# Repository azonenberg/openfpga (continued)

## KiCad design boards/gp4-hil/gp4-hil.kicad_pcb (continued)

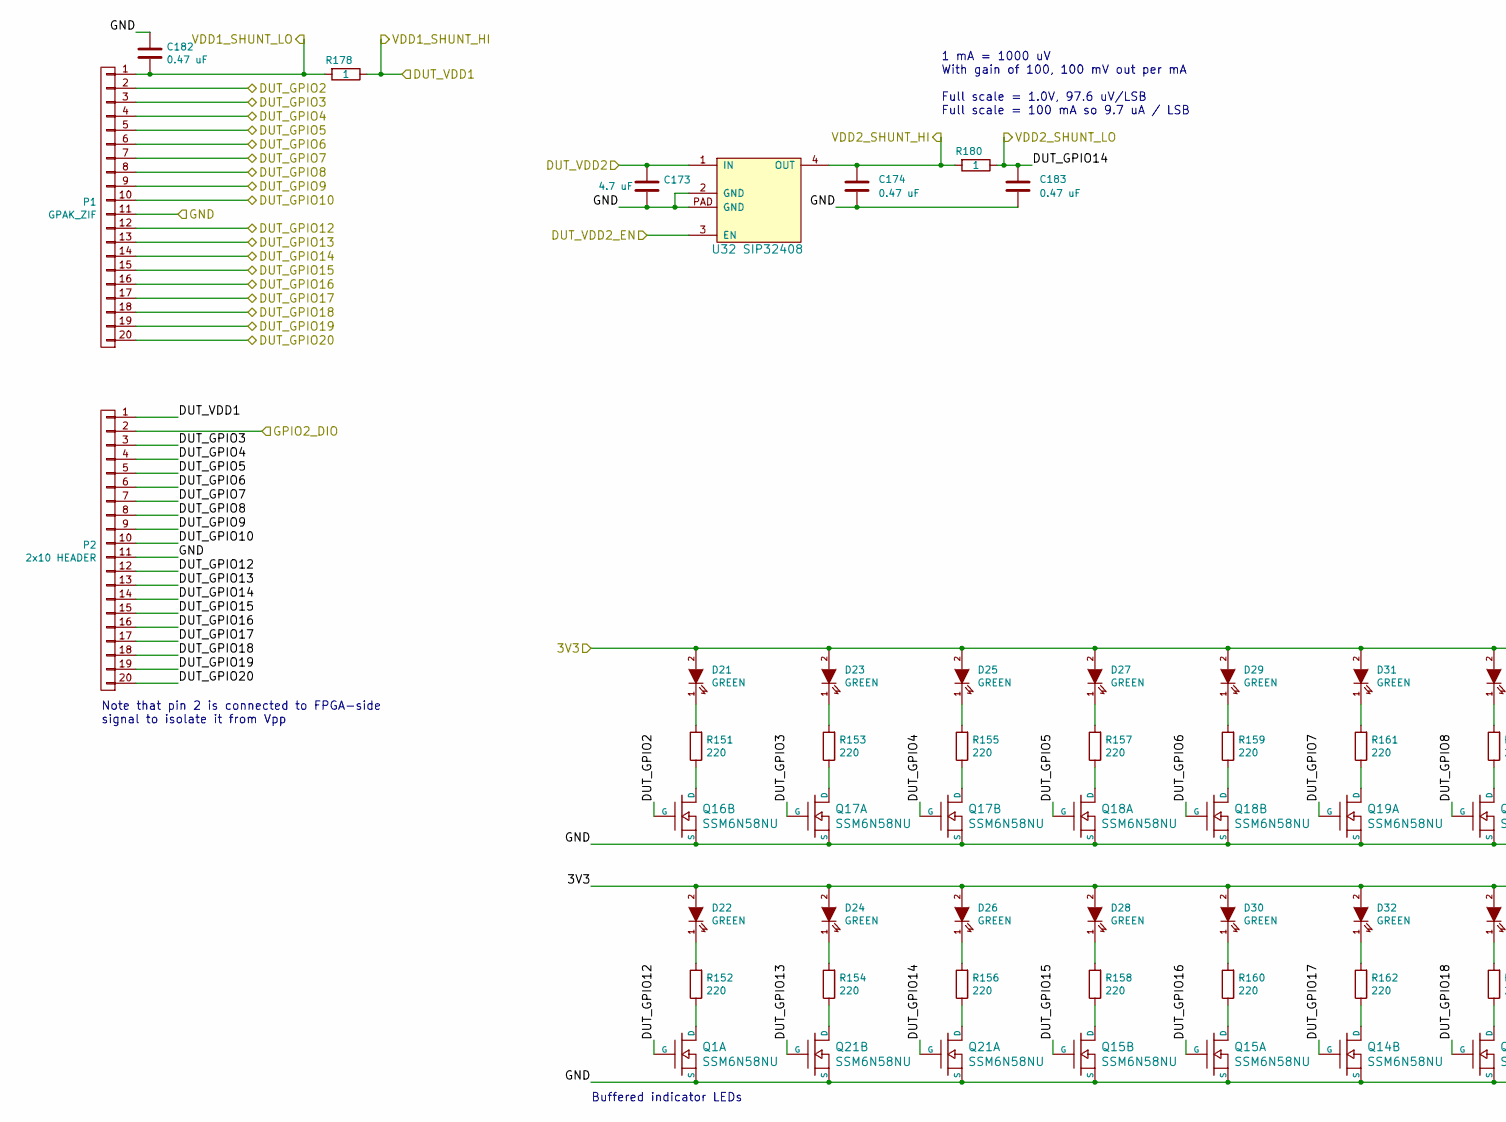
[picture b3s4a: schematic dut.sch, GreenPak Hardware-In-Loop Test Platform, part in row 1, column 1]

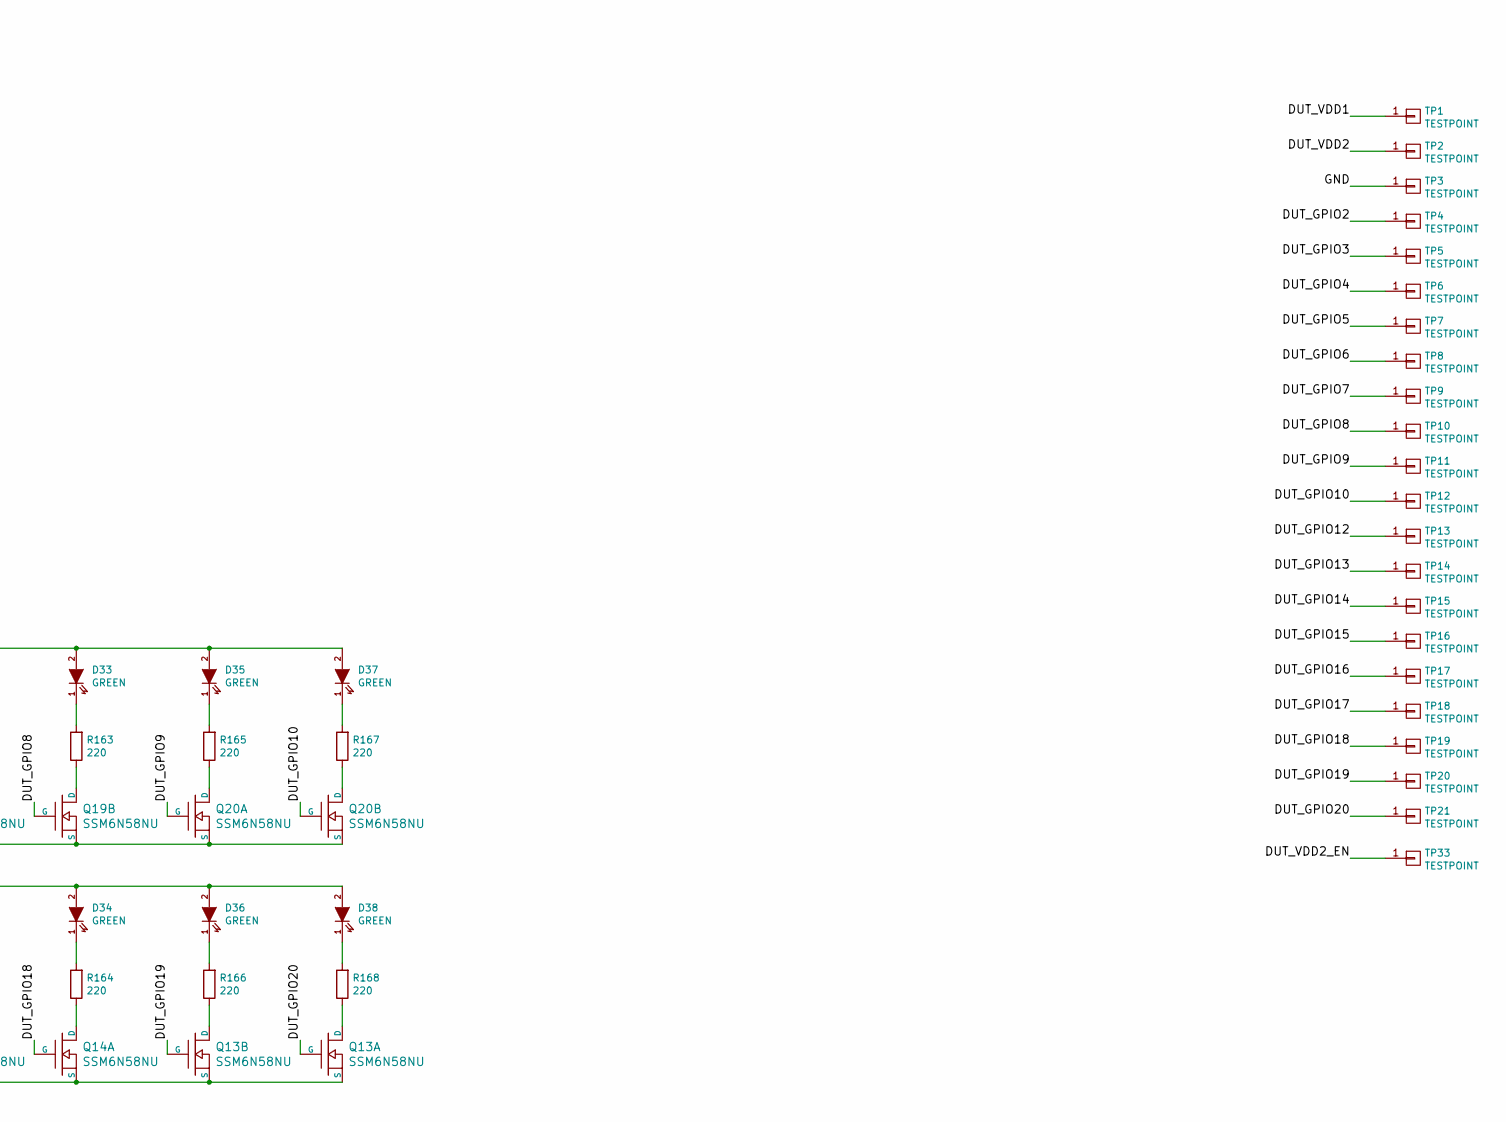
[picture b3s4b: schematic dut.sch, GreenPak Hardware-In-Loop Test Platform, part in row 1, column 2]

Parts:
C173: 4.7 uF; EIA_0603_CAP_NOSILK
C174, C182, C183: 0.47 uF; EIA_0402_CAP_NOSILK
D21, D22, D23, D24, D25, D26, D27, D28, D29, D30, D31, D32, D33, D34, D35, D36, D37, D38: GREEN; EIA_0603_LED
P1: GPAK_ZIF; CONN_HEADER_2.54MM_2x10_RA_TRORIG
P2: 2x10 HEADER; CONN_HEADER_2.54MM_2x10_RA_TRORIG
Q1, Q13, Q14, Q15, Q16, Q17, Q18, Q19, Q20, Q21: SSM6N58NU; DFN_6_0.65MM_2x2MM_GDS
R151, R152, R153, R154, R155, R156, R157, R158, R159, R160, R161, R162, R163, R164, R165, R166, R167, R168: 220; EIA_0402_RES_NOSILK
R178, R180: 1; EIA_0402_RES_NOSILK
TP1, TP2, TP3, TP4, TP5, TP6, TP7, TP8, TP9, TP10, TP11, TP12, TP13, TP14, TP15, TP16, TP17, TP18, TP19, TP20, TP21: TESTPOINT; TESTPOINT_SMT_KEYSTONE_5016
TP33: TESTPOINT; TESTPOINT_SMT_0.5MM
U32: SIP32408; DFN_4_0.5MM_1.6x1.2MM

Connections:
/Analog IO/3V3: D21.2 (A), D22.2 (A), D23.2 (A), D24.2 (A), D25.2 (A), D26.2 (A), D27.2 (A), D28.2 (A), D29.2 (A), D30.2 (A), D31.2 (A), D32.2 (A), D33.2 (A), D34.2 (A), D35.2 (A), D36.2 (A), D37.2 (A), D38.2 (A); also elsewhere on the board
/Analog IO/DUT_GPIO2: P1.2, Q16.G2 (G), TP4.1; also elsewhere on the board
/Analog IO/DUT_GPIO3: P1.3, P2.3, Q17.G1 (G), TP5.1; also elsewhere on the board
/Analog IO/DUT_GPIO4: P1.4, P2.4, Q17.G2 (G), TP6.1; also elsewhere on the board
/Analog IO/DUT_GPIO5: P1.5, P2.5, Q18.G1 (G), TP7.1; also elsewhere on the board
/Analog IO/DUT_GPIO6: P1.6, P2.6, Q18.G2 (G), TP8.1; also elsewhere on the board
/Analog IO/DUT_GPIO7: P1.7, P2.7, Q19.G1 (G), TP9.1; also elsewhere on the board
/Analog IO/DUT_GPIO8: P1.8, P2.8, Q19.G2 (G), TP10.1; also elsewhere on the board
/Analog IO/DUT_GPIO9: P1.9, P2.9, Q20.G1 (G), TP11.1; also elsewhere on the board
/Analog IO/DUT_GPIO10: P1.10, P2.10, Q20.G2 (G), TP12.1; also elsewhere on the board
/Analog IO/DUT_GPIO12: P1.12, P2.12, Q1.G1 (G), TP13.1; also elsewhere on the board
/Analog IO/DUT_GPIO13: P1.13, P2.13, Q21.G2 (G), TP14.1; also elsewhere on the board
/Analog IO/DUT_GPIO14: C183.1, P1.14, P2.14, Q21.G1 (G), R180.1, TP15.1; also elsewhere on the board
/Analog IO/DUT_GPIO15: P1.15, P2.15, Q15.G2 (G), TP16.1; also elsewhere on the board
/Analog IO/DUT_GPIO16: P1.16, P2.16, Q15.G1 (G), TP17.1; also elsewhere on the board
/Analog IO/DUT_GPIO17: P1.17, P2.17, Q14.G2 (G), TP18.1; also elsewhere on the board
/Analog IO/DUT_GPIO18: P1.18, P2.18, Q14.G1 (G), TP19.1; also elsewhere on the board
/Analog IO/DUT_GPIO19: P1.19, P2.19, Q13.G2 (G), TP20.1; also elsewhere on the board
/Analog IO/DUT_GPIO20: P1.20, P2.20, Q13.G1 (G), TP21.1; also elsewhere on the board
/Analog IO/DUT_VDD1: P2.1, R178.1, TP1.1; also elsewhere on the board
/Analog IO/DUT_VDD2: C173.1, TP2.1, U32.1 (IN); also elsewhere on the board
/Analog IO/GND: C173.2, C174.2, C182.1, C183.2, P1.11, P2.11, Q1.S1 (S), Q13.S1 (S), Q13.S2 (S), Q14.S1 (S), Q14.S2 (S), Q15.S1 (S), Q15.S2 (S), Q16.S2 (S), Q17.S1 (S), Q17.S2 (S), Q18.S1 (S), Q18.S2 (S), Q19.S1 (S), Q19.S2 (S), Q20.S1 (S), Q20.S2 (S), Q21.S1 (S), Q21.S2 (S), TP3.1, U32.2 (GND), U32.PAD (GND); also elsewhere on the board
/Analog IO/VDD1_SHUNT_LO: C182.2, P1.1, R178.2; also elsewhere on the board
/Analog IO/VDD2_SHUNT_HI: C174.1, R180.2, U32.4 (OUT); also elsewhere on the board
/DUT/DUT_VDD2_EN: TP33.1, U32.3 (EN); also elsewhere on the board
/DUT/GPIO2_DIO: P2.2; also elsewhere on the board
unnamed: D21.1 (K), R151.2
unnamed: D22.1 (K), R152.2
unnamed: D23.1 (K), R153.2
unnamed: D24.1 (K), R154.2
unnamed: D25.1 (K), R155.2
unnamed: D26.1 (K), R156.2
unnamed: D27.1 (K), R157.2
unnamed: D28.1 (K), R158.2
unnamed: D29.1 (K), R159.2
unnamed: D30.1 (K), R160.2
unnamed: D31.1 (K), R161.2
unnamed: D32.1 (K), R162.2
unnamed: D33.1 (K), R163.2
unnamed: D34.1 (K), R164.2
unnamed: D35.1 (K), R165.2
unnamed: D36.1 (K), R166.2
unnamed: D37.1 (K), R167.2
unnamed: D38.1 (K), R168.2
unnamed: Q1.D1 (D), R152.1
unnamed: Q13.D1 (D), R168.1
unnamed: Q13.D2 (D), R166.1
unnamed: Q14.D1 (D), R164.1
unnamed: Q14.D2 (D), R162.1
unnamed: Q15.D1 (D), R160.1
unnamed: Q15.D2 (D), R158.1
unnamed: Q16.D2 (D), R151.1
unnamed: Q17.D1 (D), R153.1
unnamed: Q17.D2 (D), R155.1
unnamed: Q18.D1 (D), R157.1
unnamed: Q18.D2 (D), R159.1
unnamed: Q19.D1 (D), R161.1
unnamed: Q19.D2 (D), R163.1
unnamed: Q20.D1 (D), R165.1
unnamed: Q20.D2 (D), R167.1
unnamed: Q21.D1 (D), R156.1
unnamed: Q21.D2 (D), R154.1

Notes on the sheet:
Buffered indicator LEDs
Note that pin 2 is connected to FPGA-side signal to isolate it from Vpp
1 mA = 1000 uV With gain of 100, 100 mV out per mA Full scale = 1.0V, 97.6 uV/LSB Full scale = 100 mA so 9.7 uA / LSB

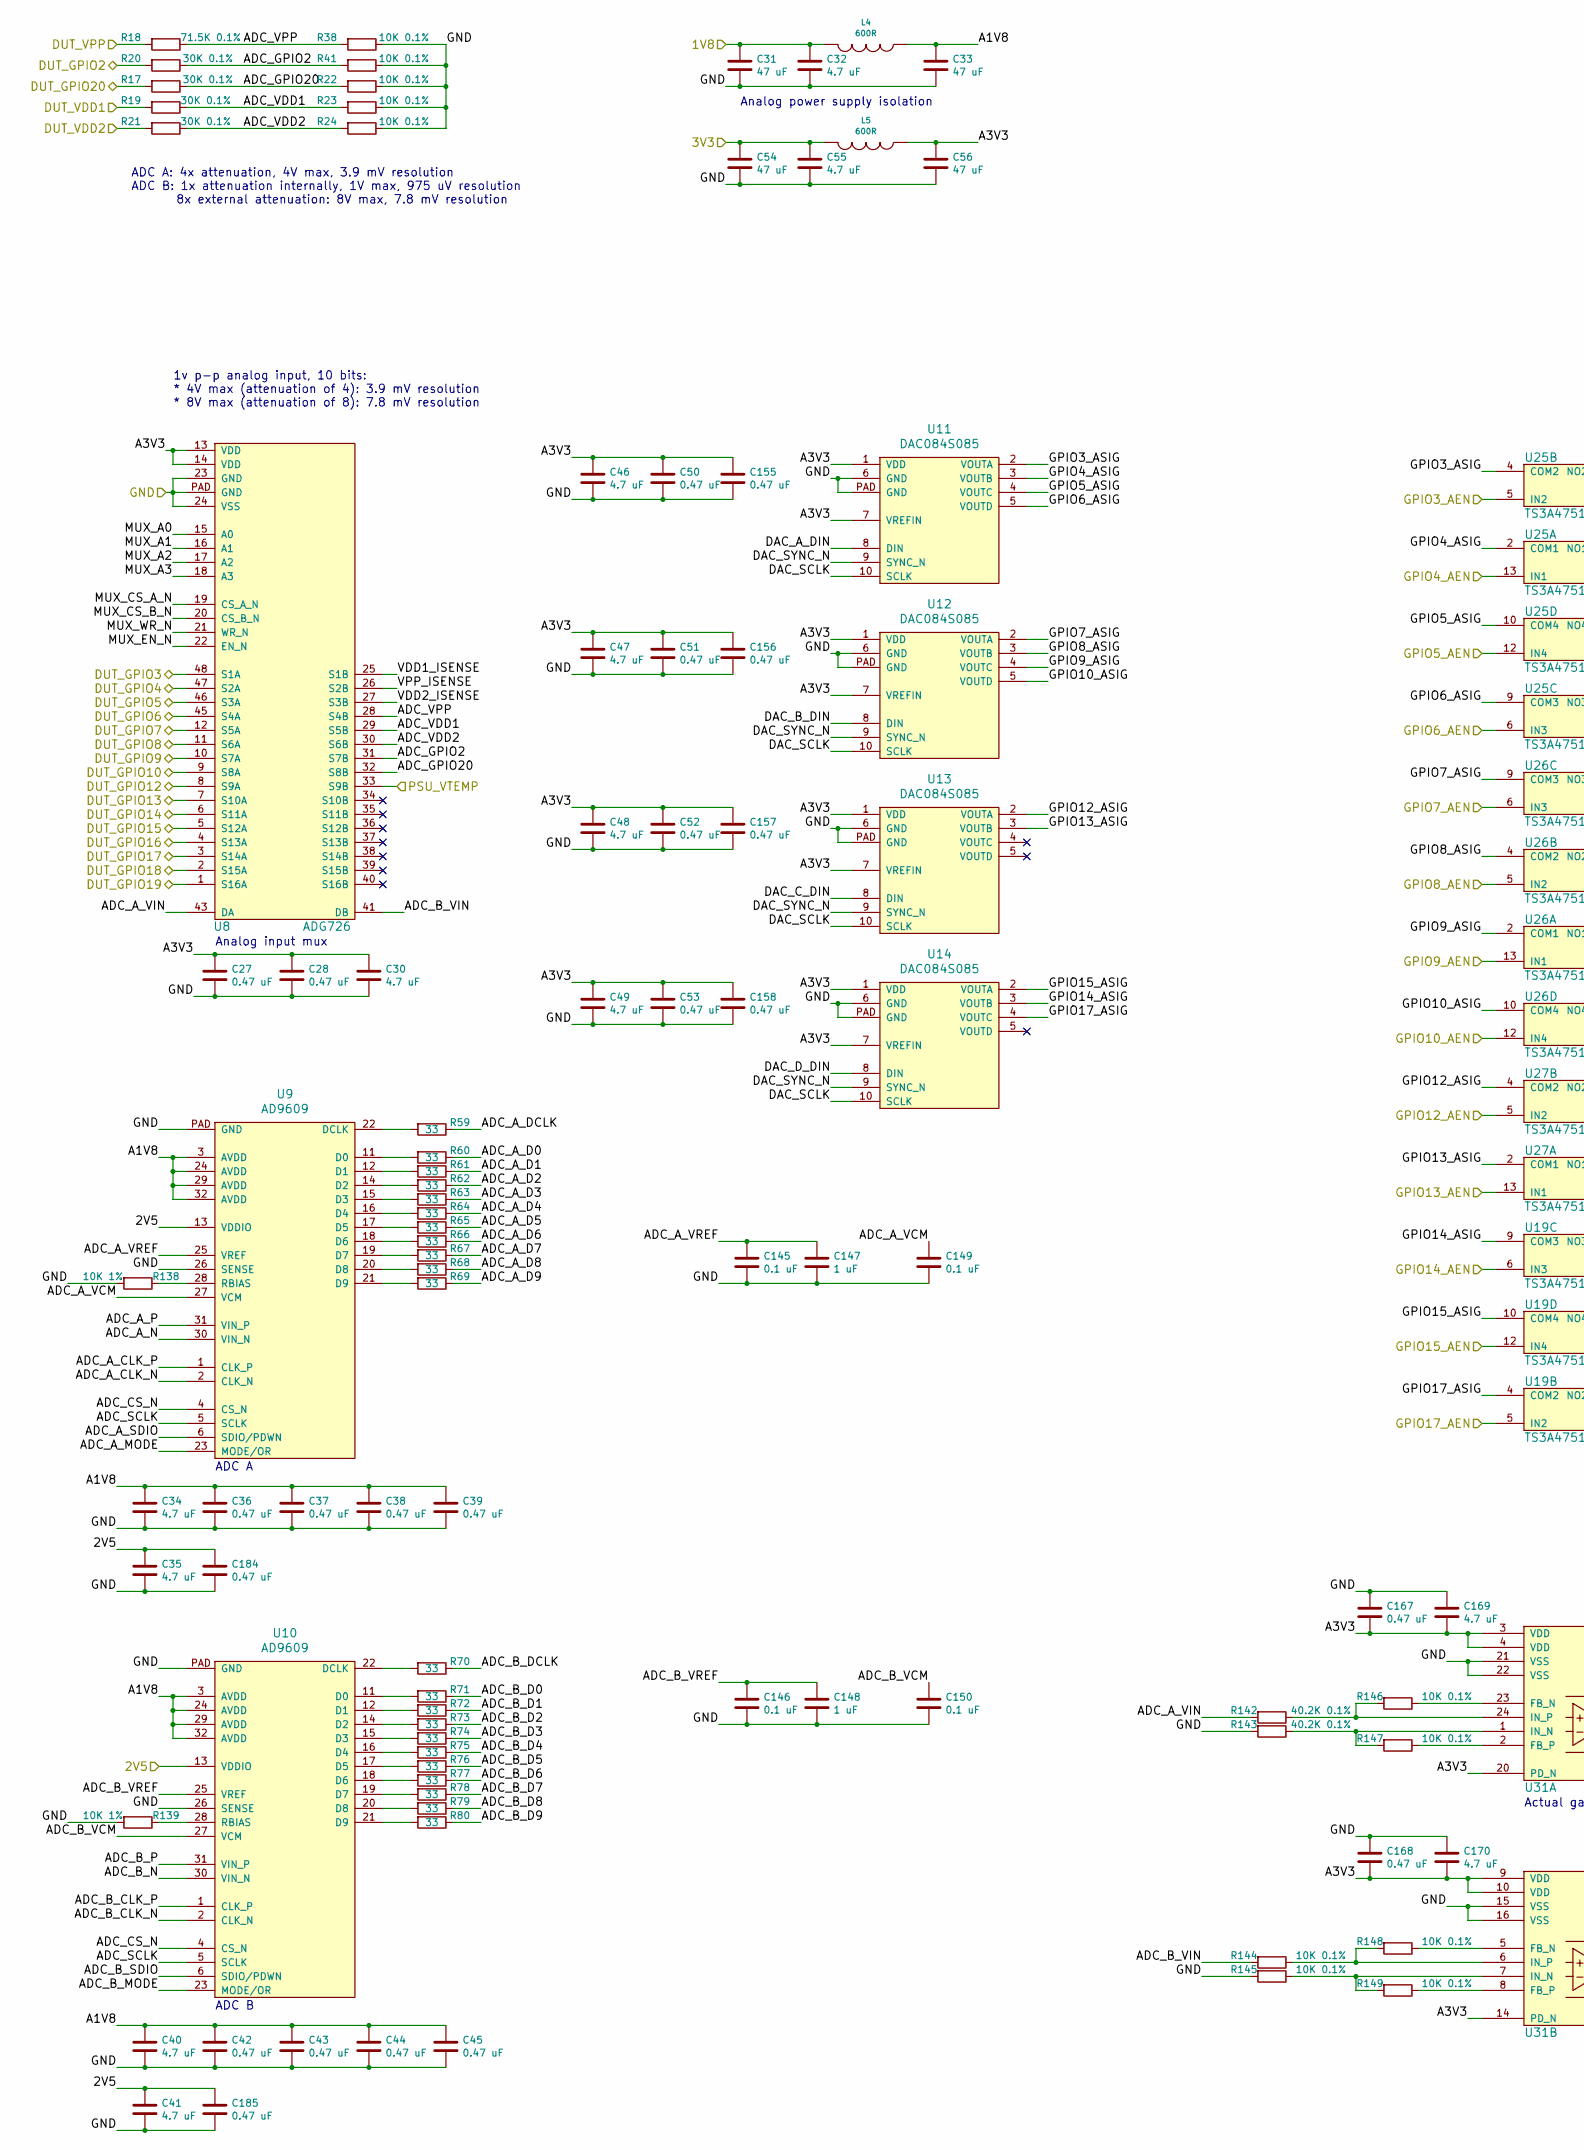
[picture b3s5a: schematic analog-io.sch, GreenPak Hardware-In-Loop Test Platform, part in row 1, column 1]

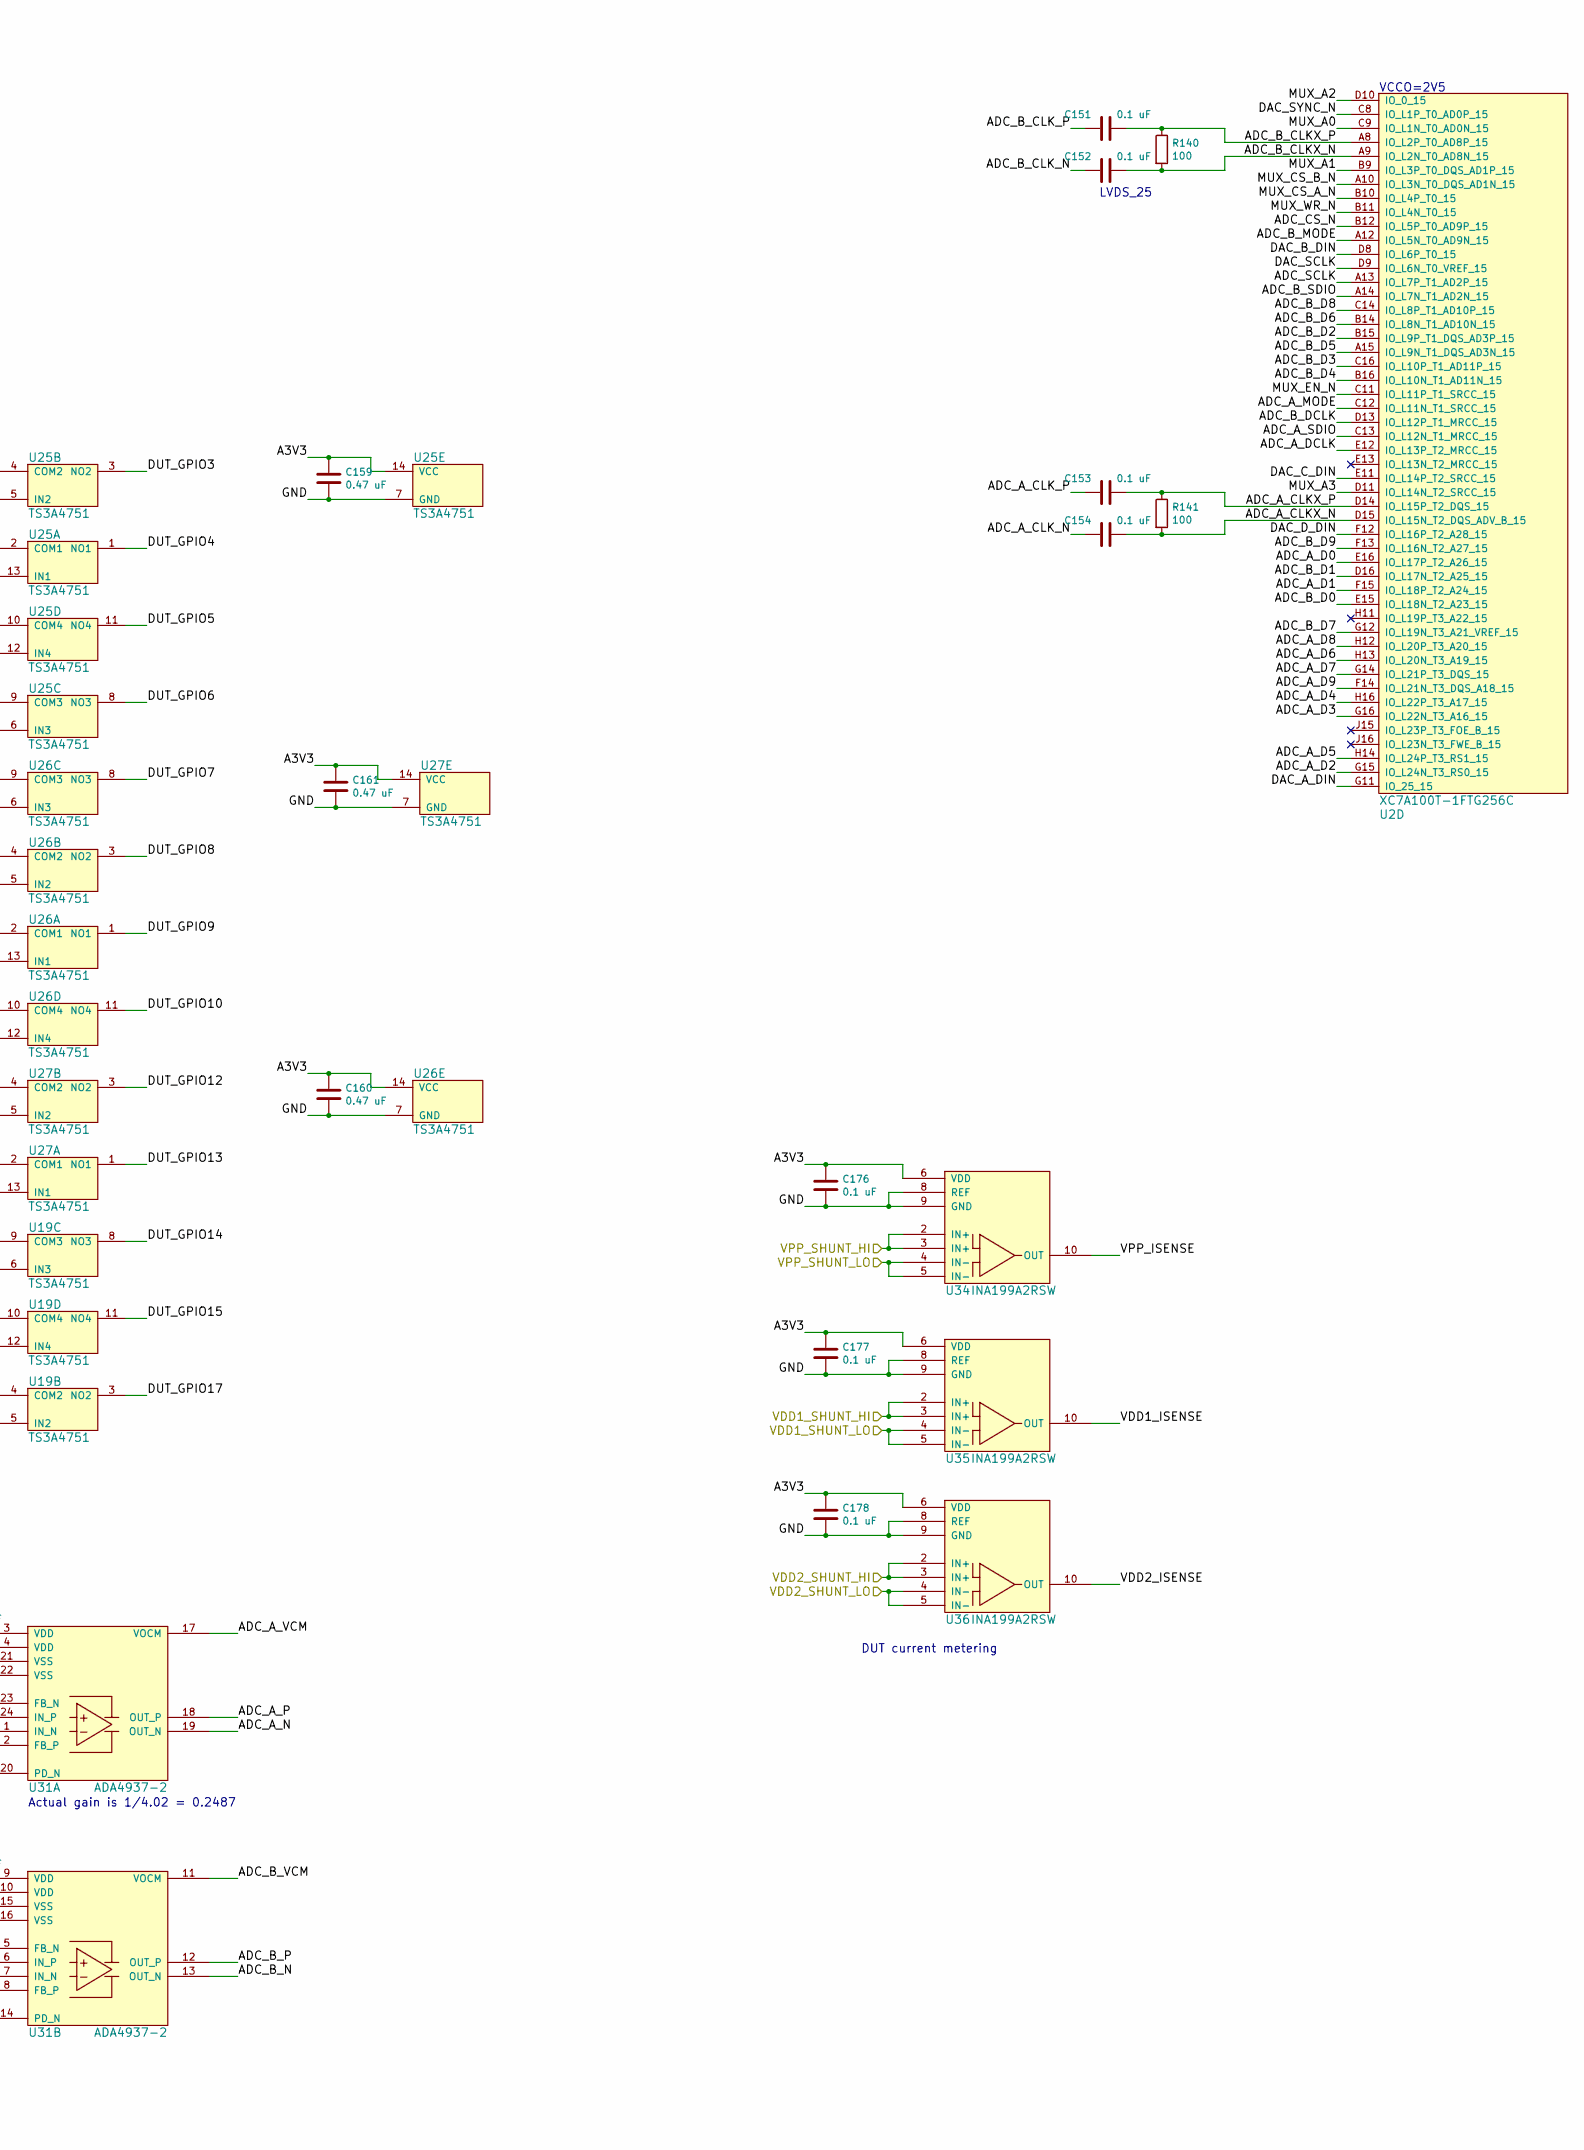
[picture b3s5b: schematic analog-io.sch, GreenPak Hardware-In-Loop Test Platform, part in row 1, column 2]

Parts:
C27, C28, C36, C37, C38, C39, C42, C43, C44, C45, C50, C51, C52, C53, C155, C156, C157, C158, C159, C160, C161, C167, C168, C184, C185: 0.47 uF; EIA_0402_CAP_NOSILK
C30, C32, C34, C35, C40, C41, C46, C47, C48, C49, C55, C169, C170: 4.7 uF; EIA_0603_CAP_NOSILK
C31, C33, C54, C56: 47 uF; EIA_1206_CAP_NOSILK
C145, C146, C149, C150, C151, C152, C153, C154, C176, C177, C178: 0.1 uF; EIA_0402_CAP_NOSILK
C147, C148: 1 uF; EIA_0402_CAP_NOSILK
L4, L5: 600R; EIA_0603_INDUCTOR_NOSILK
R17, R19, R20, R21: 30K 0.1%; EIA_0402_RES_NOSILK
R18: 71.5K 0.1%; EIA_0402_RES_NOSILK
R22, R23, R24, R38, R41, R144, R145, R146, R147, R148, R149: 10K 0.1%; EIA_0402_RES_NOSILK
R59, R60, R61, R62, R63, R64, R65, R66, R67, R68, R69, R70, R71, R72, R73, R74, R75, R76, R77, R78, R79, R80: 33; EIA_0402_RES_NOSILK
R138, R139: 10K 1%; EIA_0402_RES_NOSILK
R140, R141: 100; EIA_0402_RES_NOSILK
R142, R143: 40.2K 0.1%; EIA_0402_RES_NOSILK
U2: XC7A100T-1FTG256C; BGA_256_17x17_FULLARRAY_1MM
U8: ADG726; QFN_48_0.5MM_7x7MM
U9, U10: AD9609; QFN_32_0.5MM_5x5MM
U11, U12, U13, U14: DAC084S085; DFN_10_0.5MM_3x3MM
U19, U25, U26, U27: TS3A4751; QFN_14_0.4MM_2x2MM_TI_RUC
U31: ADA4937-2; QFN_24_0.5MM_4x4MM
U34, U35, U36: INA199A2RSW; QFN_10_0.4MM_1.8x1.5MM

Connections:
/Analog IO/1V8: C31.1, C32.1, L4.2; also elsewhere on the board
/Analog IO/2V5: C35.1, C41.1, C184.1, C185.1, U9.13 (VDDIO), U10.13 (VDDIO); also elsewhere on the board
/Analog IO/3V3: C54.1, C55.1, L5.2; also elsewhere on the board
/Analog IO/A1V8: C33.1, C34.1, C36.1, C37.1, C38.1, C39.1, C40.1, C42.1, C43.1, C44.1, C45.1, L4.1, U9.3 (AVDD), U9.24 (AVDD), U9.29 (AVDD), U9.32 (AVDD), U10.3 (AVDD), U10.24 (AVDD), U10.29 (AVDD), U10.32 (AVDD)
/Analog IO/A3V3: C27.1, C28.1, C30.1, C46.1, C47.1, C48.1, C49.1, C50.1, C51.1, C52.1, C53.1, C56.1, C155.1, C156.1, C157.1, C158.1, C159.1, C160.1, C161.1, C167.2, C168.2, C169.2, C170.2, C176.1, C177.1, C178.1, L5.1, U8.13 (VDD), U8.14 (VDD), U11.1 (VDD), U11.7 (VREFIN), U12.1 (VDD), U12.7 (VREFIN), U13.1 (VDD), U13.7 (VREFIN), U14.1 (VDD), U14.7 (VREFIN), U25.14 (VCC), U26.14 (VCC), U27.14 (VCC), U31.3 (VDD), U31.4 (VDD), U31.9 (VDD), U31.10 (VDD), U31.14 (PD_N), U31.20 (PD_N), U34.6 (VDD), U35.6 (VDD), U36.6 (VDD)
/Analog IO/ADC_A_CLKX_N: C154.1, R141.2, U2.D15 (IO_L15N_T2_DQS_ADV_B_15)
/Analog IO/ADC_A_CLKX_P: C153.1, R141.1, U2.D14 (IO_L15P_T2_DQS_15)
/Analog IO/ADC_A_CLK_N: C154.2, U9.2 (CLK_N)
/Analog IO/ADC_A_CLK_P: C153.2, U9.1 (CLK_P)
/Analog IO/ADC_A_D0: R60.1, U2.E16 (IO_L17P_T2_A26_15)
/Analog IO/ADC_A_D1: R61.1, U2.F15 (IO_L18P_T2_A24_15)
/Analog IO/ADC_A_D2: R62.1, U2.G15 (IO_L24N_T3_RS0_15)
/Analog IO/ADC_A_D3: R63.1, U2.G16 (IO_L22N_T3_A16_15)
/Analog IO/ADC_A_D4: R64.1, U2.H16 (IO_L22P_T3_A17_15)
/Analog IO/ADC_A_D5: R65.1, U2.H14 (IO_L24P_T3_RS1_15)
/Analog IO/ADC_A_D6: R66.1, U2.H13 (IO_L20N_T3_A19_15)
/Analog IO/ADC_A_D7: R67.1, U2.G14 (IO_L21P_T3_DQS_15)
/Analog IO/ADC_A_D8: R68.1, U2.H12 (IO_L20P_T3_A20_15)
/Analog IO/ADC_A_D9: R69.1, U2.F14 (IO_L21N_T3_DQS_A18_15)
/Analog IO/ADC_A_DCLK: R59.1, U2.E12 (IO_L13P_T2_MRCC_15)
/Analog IO/ADC_A_MODE: U2.C12 (IO_L11N_T1_SRCC_15), U9.23 (MODE/OR)
/Analog IO/ADC_A_N: U9.30 (VIN_N), U31.19 (OUT_N)
/Analog IO/ADC_A_P: U9.31 (VIN_P), U31.18 (OUT_P)
/Analog IO/ADC_A_SDIO: U2.C13 (IO_L12N_T1_MRCC_15), U9.6 (SDIO/PDWN)
/Analog IO/ADC_A_VCM: C149.1, U9.27 (VCM), U31.17 (VOCM)
/Analog IO/ADC_A_VIN: R142.2, U8.43 (DA)
/Analog IO/ADC_A_VREF: C145.1, C147.1, U9.25 (VREF)
/Analog IO/ADC_B_CLKX_N: C152.1, R140.2, U2.A9 (IO_L2N_T0_AD8N_15)
/Analog IO/ADC_B_CLKX_P: C151.1, R140.1, U2.A8 (IO_L2P_T0_AD8P_15)
/Analog IO/ADC_B_CLK_N: C152.2, U10.2 (CLK_N)
/Analog IO/ADC_B_CLK_P: C151.2, U10.1 (CLK_P)
/Analog IO/ADC_B_D0: R71.1, U2.E15 (IO_L18N_T2_A23_15)
/Analog IO/ADC_B_D1: R72.1, U2.D16 (IO_L17N_T2_A25_15)
/Analog IO/ADC_B_D2: R73.1, U2.B15 (IO_L9P_T1_DQS_AD3P_15)
/Analog IO/ADC_B_D3: R74.1, U2.C16 (IO_L10P_T1_AD11P_15)
/Analog IO/ADC_B_D4: R75.1, U2.B16 (IO_L10N_T1_AD11N_15)
/Analog IO/ADC_B_D5: R76.1, U2.A15 (IO_L9N_T1_DQS_AD3N_15)
/Analog IO/ADC_B_D6: R77.1, U2.B14 (IO_L8N_T1_AD10N_15)
/Analog IO/ADC_B_D7: R78.1, U2.G12 (IO_L19N_T3_A21_VREF_15)
/Analog IO/ADC_B_D8: R79.1, U2.C14 (IO_L8P_T1_AD10P_15)
/Analog IO/ADC_B_D9: R80.1, U2.F13 (IO_L16N_T2_A27_15)
/Analog IO/ADC_B_DCLK: R70.1, U2.D13 (IO_L12P_T1_MRCC_15)
/Analog IO/ADC_B_MODE: U2.A12 (IO_L5N_T0_AD9N_15), U10.23 (MODE/OR)
/Analog IO/ADC_B_N: U10.30 (VIN_N), U31.13 (OUT_N)
/Analog IO/ADC_B_P: U10.31 (VIN_P), U31.12 (OUT_P)
/Analog IO/ADC_B_SDIO: U2.A14 (IO_L7N_T1_AD2N_15), U10.6 (SDIO/PDWN)
/Analog IO/ADC_B_VCM: C150.1, U10.27 (VCM), U31.11 (VOCM)
/Analog IO/ADC_B_VIN: R144.2, U8.41 (DB)
/Analog IO/ADC_B_VREF: C146.1, C148.1, U10.25 (VREF)
/Analog IO/ADC_CS_N: U2.B12 (IO_L5P_T0_AD9P_15), U9.4 (CS_N), U10.4 (CS_N)
/Analog IO/ADC_GPIO2: R20.1, R41.2, U8.31 (S7B)
/Analog IO/ADC_GPIO20: R17.1, R22.2, U8.32 (S8B)
/Analog IO/ADC_SCLK: U2.A13 (IO_L7P_T1_AD2P_15), U9.5 (SCLK), U10.5 (SCLK)
/Analog IO/ADC_VDD1: R19.1, R23.2, U8.29 (S5B)
/Analog IO/ADC_VDD2: R21.1, R24.2, U8.30 (S6B)
/Analog IO/ADC_VPP: R18.1, R38.2, U8.28 (S4B)
/Analog IO/DAC_A_DIN: U2.G11 (IO_25_15), U11.8 (DIN)
/Analog IO/DAC_B_DIN: U2.D8 (IO_L6P_T0_15), U12.8 (DIN)
/Analog IO/DAC_C_DIN: U2.E11 (IO_L14P_T2_SRCC_15), U13.8 (DIN)
/Analog IO/DAC_D_DIN: U2.F12 (IO_L16P_T2_A28_15), U14.8 (DIN)
/Analog IO/DAC_SCLK: U2.D9 (IO_L6N_T0_VREF_15), U11.10 (SCLK), U12.10 (SCLK), U13.10 (SCLK), U14.10 (SCLK)
/Analog IO/DAC_SYNC_N: U2.C8 (IO_L1P_T0_AD0P_15), U11.9 (SYNC_N), U12.9 (SYNC_N), U13.9 (SYNC_N), U14.9 (SYNC_N)
/Analog IO/DUT_GPIO2: R20.2, U34.4 (IN-), U34.5 (IN-); also elsewhere on the board
/Analog IO/DUT_GPIO3: U8.48 (S1A), U25.3 (NO2); also elsewhere on the board
/Analog IO/DUT_GPIO4: U8.47 (S2A), U25.1 (NO1); also elsewhere on the board
/Analog IO/DUT_GPIO5: U8.46 (S3A), U25.11 (NO4); also elsewhere on the board
/Analog IO/DUT_GPIO6: U8.45 (S4A), U25.8 (NO3); also elsewhere on the board
/Analog IO/DUT_GPIO7: U8.12 (S5A), U26.8 (NO3); also elsewhere on the board
/Analog IO/DUT_GPIO8: U8.11 (S6A), U26.3 (NO2); also elsewhere on the board
/Analog IO/DUT_GPIO9: U8.10 (S7A), U26.1 (NO1); also elsewhere on the board
/Analog IO/DUT_GPIO10: U8.9 (S8A), U26.11 (NO4); also elsewhere on the board
/Analog IO/DUT_GPIO12: U8.8 (S9A), U27.3 (NO2); also elsewhere on the board
/Analog IO/DUT_GPIO13: U8.7 (S10A), U27.1 (NO1); also elsewhere on the board
/Analog IO/DUT_GPIO14: U8.6 (S11A), U19.8 (NO3), U36.4 (IN-), U36.5 (IN-); also elsewhere on the board
/Analog IO/DUT_GPIO15: U8.5 (S12A), U19.11 (NO4); also elsewhere on the board
/Analog IO/DUT_GPIO16: U8.4 (S13A); also elsewhere on the board
/Analog IO/DUT_GPIO17: U8.3 (S14A), U19.3 (NO2); also elsewhere on the board
/Analog IO/DUT_GPIO18: U8.2 (S15A); also elsewhere on the board
/Analog IO/DUT_GPIO19: U8.1 (S16A); also elsewhere on the board
/Analog IO/DUT_GPIO20: R17.2; also elsewhere on the board
/Analog IO/DUT_VDD1: R19.2, U35.2 (IN+), U35.3 (IN+); also elsewhere on the board
/Analog IO/DUT_VDD2: R21.2; also elsewhere on the board
/Analog IO/DUT_VPP: R18.2; also elsewhere on the board
/Analog IO/GND: C27.2, C28.2, C30.2, C31.2, C32.2, C33.2, C34.2, C35.2, C36.2, C37.2, C38.2, C39.2, C40.2, C41.2, C42.2, C43.2, C44.2, C45.2, C46.2, C47.2, C48.2, C49.2, C50.2, C51.2, C52.2, C53.2, C54.2, C55.2, C56.2, C145.2, C146.2, C147.2, C148.2, C149.2, C150.2, C155.2, C156.2, C157.2, C158.2, C159.2, C160.2, C161.2, C167.1, C168.1, C169.1, C170.1, C176.2, C177.2, C178.2, C184.2, C185.2, R22.1, R23.1, R24.1, R38.1, R41.1, R138.2, R139.2, R143.2, R145.2, U8.23 (GND), U8.24 (VSS), U8.PAD (GND), U9.26 (SENSE), U9.PAD (GND), U10.26 (SENSE), U10.PAD (GND), U11.6 (GND), U11.PAD (GND), U12.6 (GND), U12.PAD (GND), U13.6 (GND), U13.PAD (GND), U14.6 (GND), U14.PAD (GND), U25.7 (GND), U26.7 (GND), U27.7 (GND), U31.15 (VSS), U31.16 (VSS), U31.21 (VSS), U31.22 (VSS), U34.8 (REF), U34.9 (GND), U35.8 (REF), U35.9 (GND), U36.8 (REF), U36.9 (GND); also elsewhere on the board
/Analog IO/GPIO3_AEN: U25.5 (IN2); also elsewhere on the board
/Analog IO/GPIO3_ASIG: U11.2 (VOUTA), U25.4 (COM2)
/Analog IO/GPIO4_AEN: U25.13 (IN1); also elsewhere on the board
/Analog IO/GPIO4_ASIG: U11.3 (VOUTB), U25.2 (COM1)
/Analog IO/GPIO5_AEN: U25.12 (IN4); also elsewhere on the board
/Analog IO/GPIO5_ASIG: U11.4 (VOUTC), U25.10 (COM4)
/Analog IO/GPIO6_AEN: U25.6 (IN3); also elsewhere on the board
/Analog IO/GPIO6_ASIG: U11.5 (VOUTD), U25.9 (COM3)
/Analog IO/GPIO7_AEN: U26.6 (IN3); also elsewhere on the board
/Analog IO/GPIO7_ASIG: U12.2 (VOUTA), U26.9 (COM3)
/Analog IO/GPIO8_AEN: U26.5 (IN2); also elsewhere on the board
/Analog IO/GPIO8_ASIG: U12.3 (VOUTB), U26.4 (COM2)
/Analog IO/GPIO9_AEN: U26.13 (IN1); also elsewhere on the board
/Analog IO/GPIO9_ASIG: U12.4 (VOUTC), U26.2 (COM1)
/Analog IO/GPIO10_AEN: U26.12 (IN4); also elsewhere on the board
/Analog IO/GPIO10_ASIG: U12.5 (VOUTD), U26.10 (COM4)
/Analog IO/GPIO12_AEN: U27.5 (IN2); also elsewhere on the board
/Analog IO/GPIO12_ASIG: U13.2 (VOUTA), U27.4 (COM2)
/Analog IO/GPIO13_AEN: U27.13 (IN1); also elsewhere on the board
/Analog IO/GPIO13_ASIG: U13.3 (VOUTB), U27.2 (COM1)
/Analog IO/GPIO14_AEN: U19.6 (IN3); also elsewhere on the board
/Analog IO/GPIO14_ASIG: U14.3 (VOUTB), U19.9 (COM3)
/Analog IO/GPIO15_AEN: U19.12 (IN4); also elsewhere on the board
/Analog IO/GPIO15_ASIG: U14.2 (VOUTA), U19.10 (COM4)
/Analog IO/GPIO17_AEN: U19.5 (IN2); also elsewhere on the board
/Analog IO/GPIO17_ASIG: U14.4 (VOUTC), U19.4 (COM2)
/Analog IO/MUX_A0: U2.C9 (IO_L1N_T0_AD0N_15), U8.15 (A0)
/Analog IO/MUX_A1: U2.B9 (IO_L3P_T0_DQS_AD1P_15), U8.16 (A1)
/Analog IO/MUX_A2: U2.D10 (IO_0_15), U8.17 (A2)
/Analog IO/MUX_A3: U2.D11 (IO_L14N_T2_SRCC_15), U8.18 (A3)
/Analog IO/MUX_CS_A_N: U2.B10 (IO_L4P_T0_15), U8.19 (CS_A_N)
/Analog IO/MUX_CS_B_N: U2.A10 (IO_L3N_T0_DQS_AD1N_15), U8.20 (CS_B_N)
/Analog IO/MUX_EN_N: U2.C11 (IO_L11P_T1_SRCC_15), U8.22 (EN_N)
/Analog IO/MUX_WR_N: U2.B11 (IO_L4N_T0_15), U8.21 (WR_N)
/Analog IO/PSU_VTEMP: U8.33 (S9B); also elsewhere on the board
/Analog IO/VDD1_ISENSE: U8.25 (S1B), U35.10 (OUT)
/Analog IO/VDD1_SHUNT_LO: U35.4 (IN-), U35.5 (IN-); also elsewhere on the board
/Analog IO/VDD2_ISENSE: U8.27 (S3B), U36.10 (OUT)
/Analog IO/VDD2_SHUNT_HI: U36.2 (IN+), U36.3 (IN+); also elsewhere on the board
/Analog IO/VPP_ISENSE: U8.26 (S2B), U34.10 (OUT)
/Analog IO/VPP_SHUNT_HI: U34.2 (IN+), U34.3 (IN+); also elsewhere on the board
unnamed: R59.2, U9.22 (DCLK)
unnamed: R60.2, U9.11 (D0)
unnamed: R61.2, U9.12 (D1)
unnamed: R62.2, U9.14 (D2)
unnamed: R63.2, U9.15 (D3)
unnamed: R64.2, U9.16 (D4)
unnamed: R65.2, U9.17 (D5)
unnamed: R66.2, U9.18 (D6)
unnamed: R67.2, U9.19 (D7)
unnamed: R68.2, U9.20 (D8)
unnamed: R69.2, U9.21 (D9)
unnamed: R70.2, U10.22 (DCLK)
unnamed: R71.2, U10.11 (D0)
unnamed: R72.2, U10.12 (D1)
unnamed: R73.2, U10.14 (D2)
unnamed: R74.2, U10.15 (D3)
unnamed: R75.2, U10.16 (D4)
unnamed: R76.2, U10.17 (D5)
unnamed: R77.2, U10.18 (D6)
unnamed: R78.2, U10.19 (D7)
unnamed: R79.2, U10.20 (D8)
unnamed: R80.2, U10.21 (D9)
unnamed: R138.1, U9.28 (RBIAS)
unnamed: R139.1, U10.28 (RBIAS)
unnamed: R142.1, R146.2, U31.24 (IN_P)
unnamed: R143.1, R147.2, U31.1 (IN_N)
unnamed: R144.1, R148.2, U31.6 (IN_P)
unnamed: R145.1, R149.2, U31.7 (IN_N)
unnamed: R146.1, U31.23 (FB_N)
unnamed: R147.1, U31.2 (FB_P)
unnamed: R148.1, U31.5 (FB_N)
unnamed: R149.1, U31.8 (FB_P)

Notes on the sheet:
1v p-p analog input, 10 bits: * 4V max (attenuation of 4): 3.9 mV resolution * 8V max (attenuation of 8): 7.8 mV resolution
Analog input mux
DUT current metering
Analog power supply isolation
ADC A
ADC B
VCCO=2V5
LVDS_25
ADC A: 4x attenuation, 4V max, 3.9 mV resolution ADC B: 1x attenuation internally, 1V max, 975 uV resolution 8x external attenuation: 8V max, 7.8 mV resolution
Actual gain is 1/4.02 = 0.2487
